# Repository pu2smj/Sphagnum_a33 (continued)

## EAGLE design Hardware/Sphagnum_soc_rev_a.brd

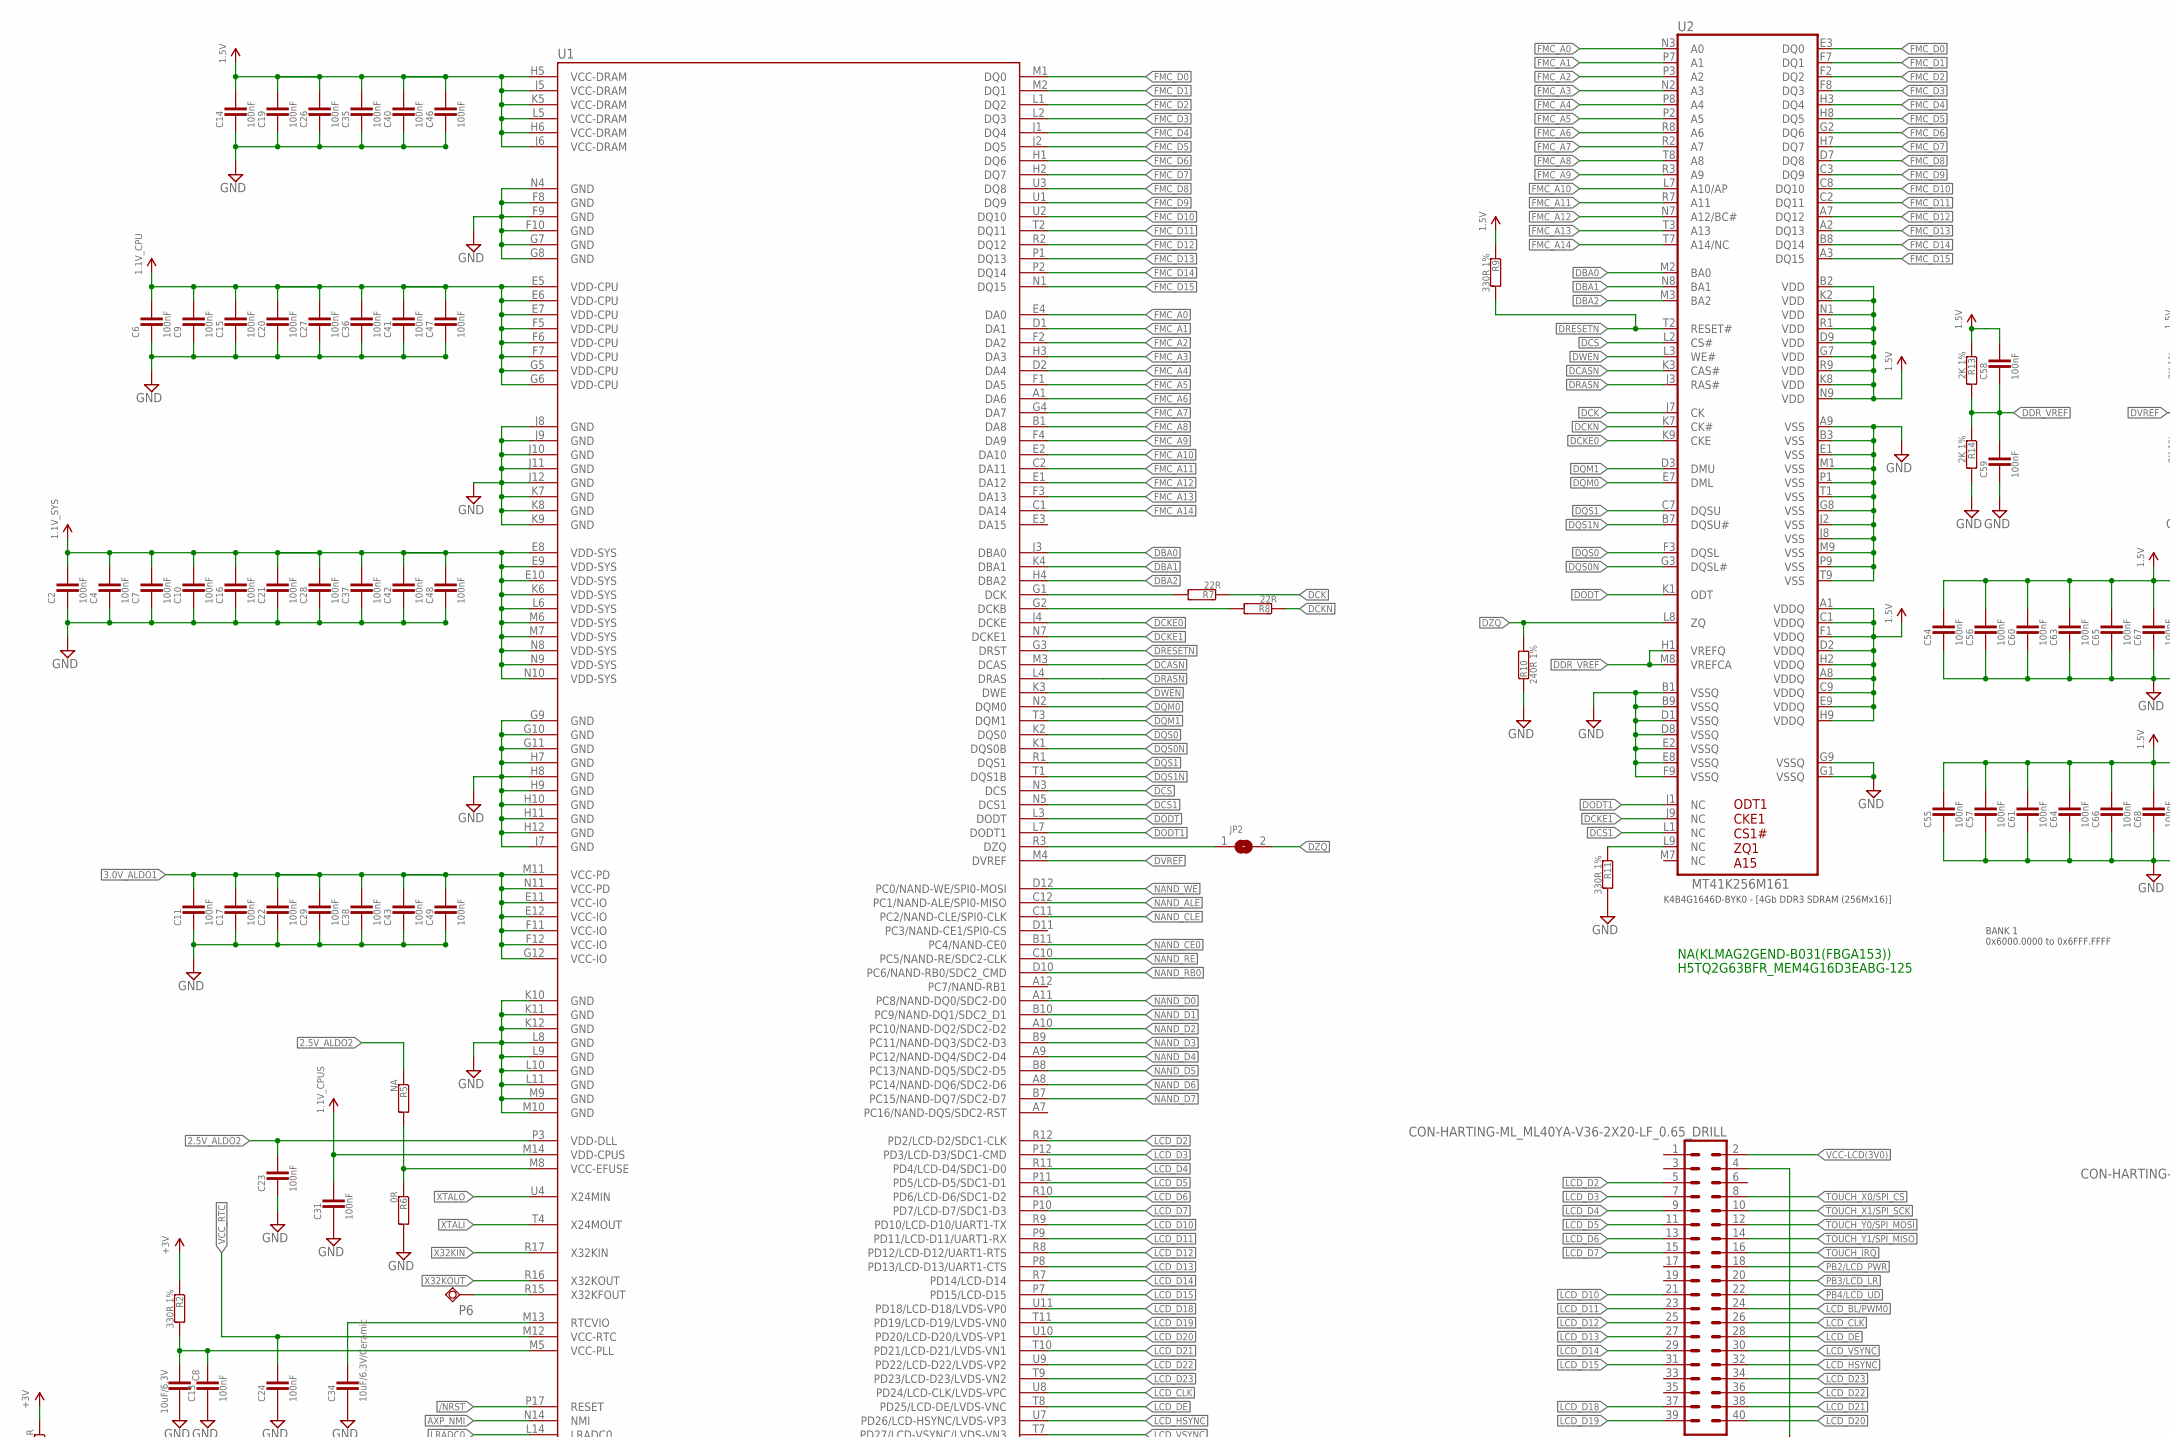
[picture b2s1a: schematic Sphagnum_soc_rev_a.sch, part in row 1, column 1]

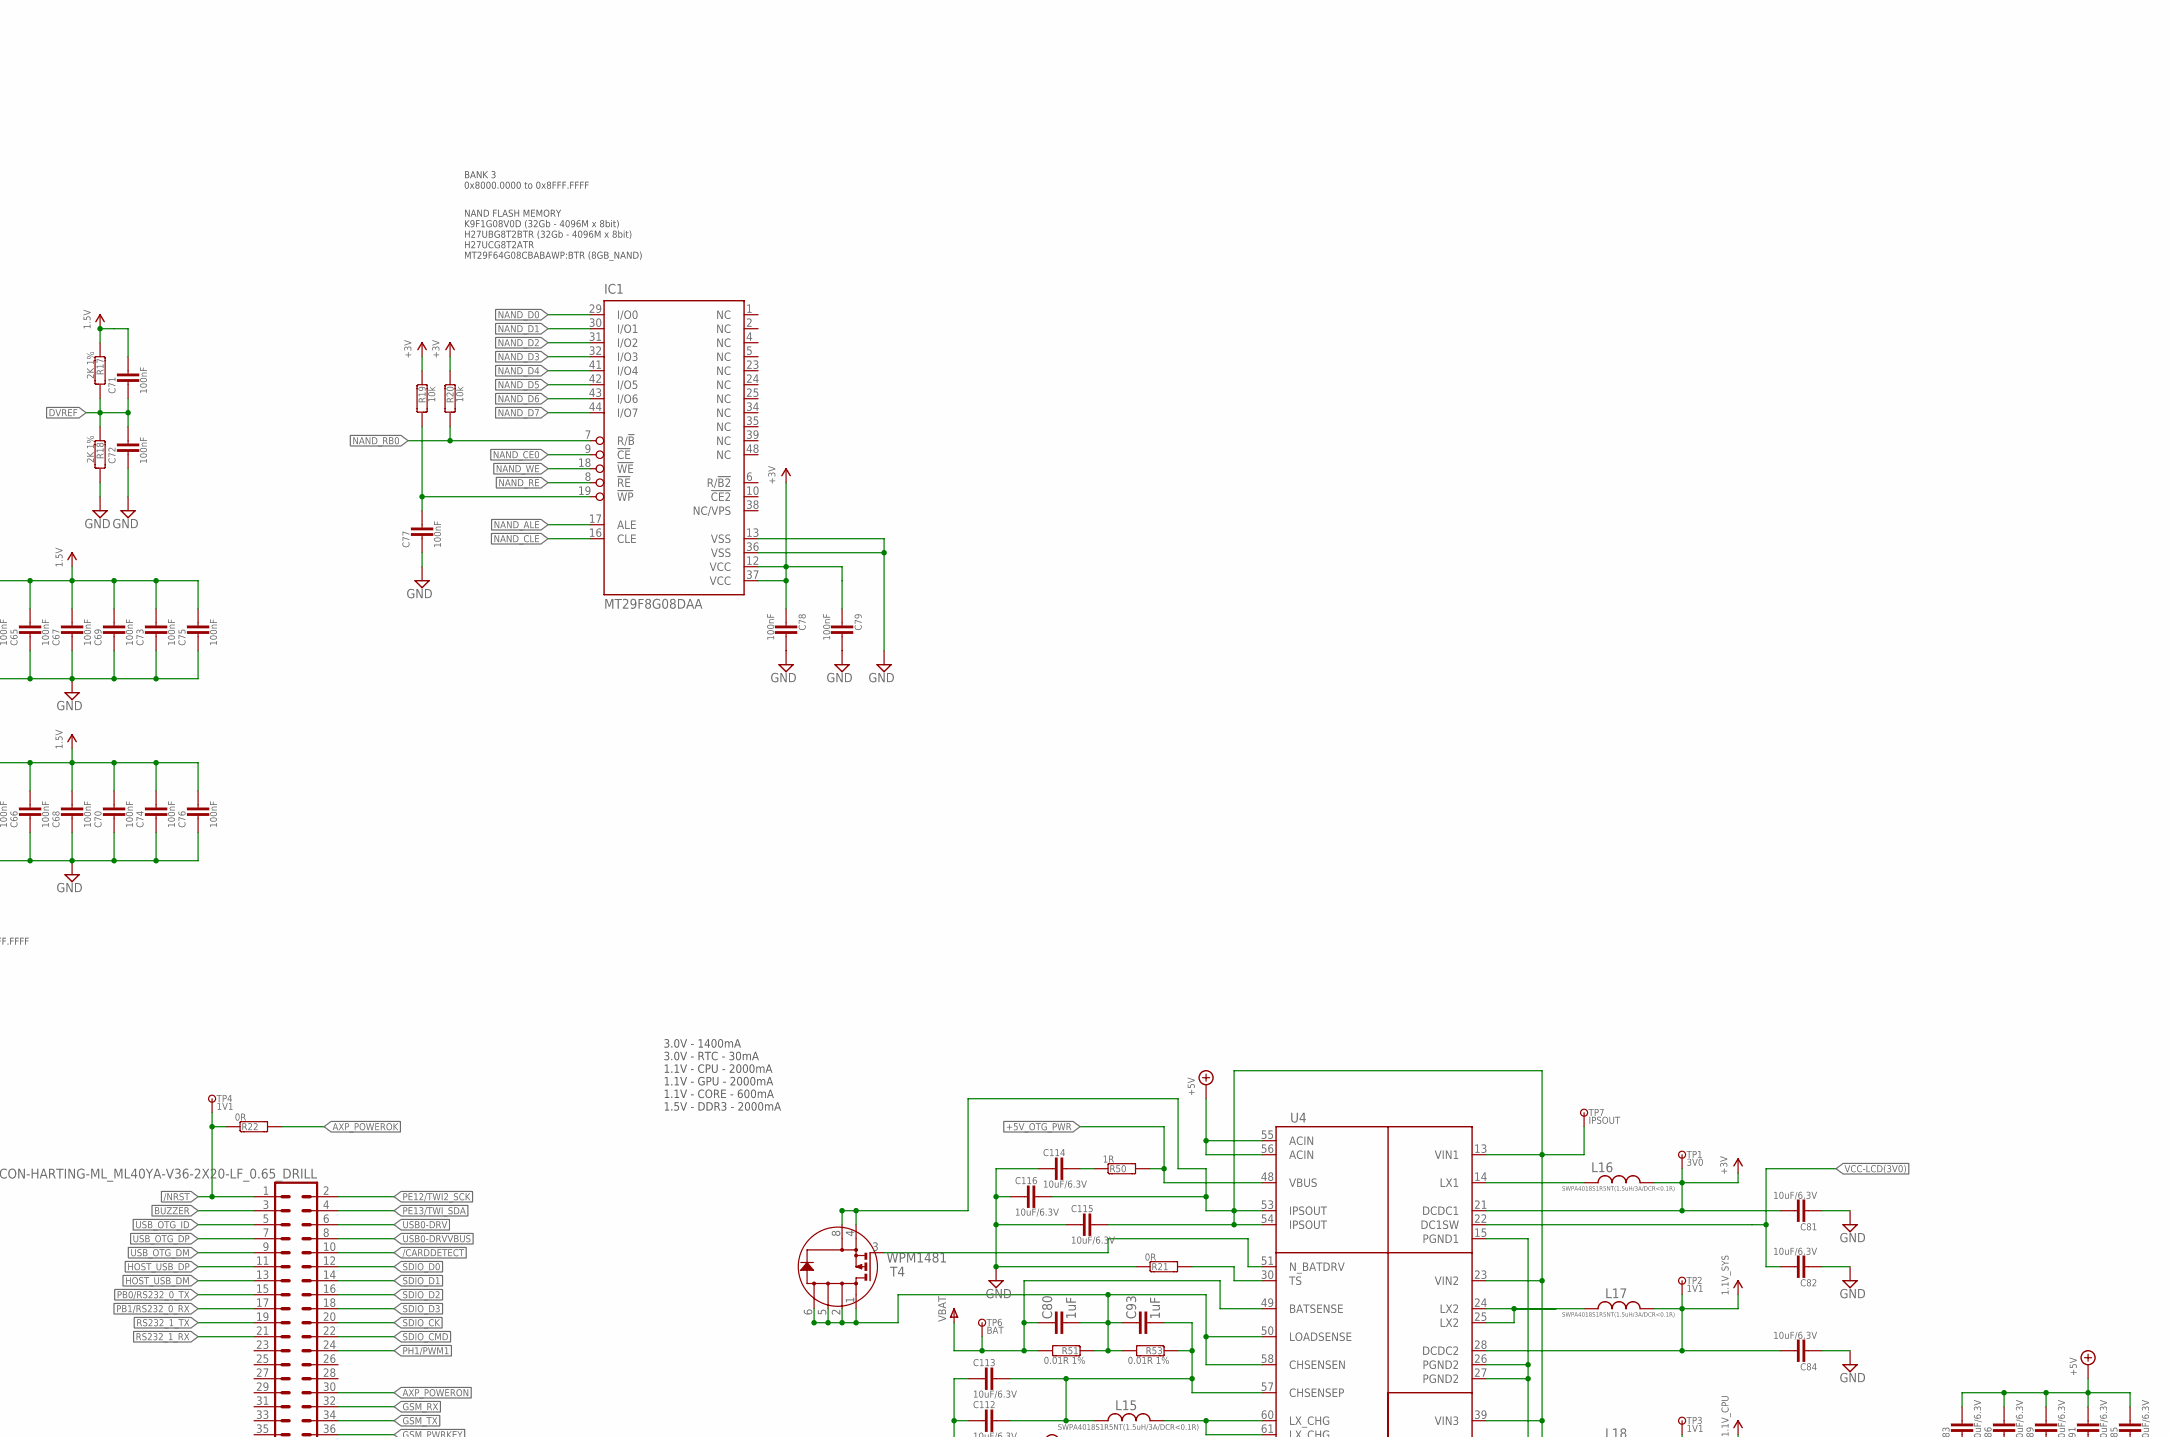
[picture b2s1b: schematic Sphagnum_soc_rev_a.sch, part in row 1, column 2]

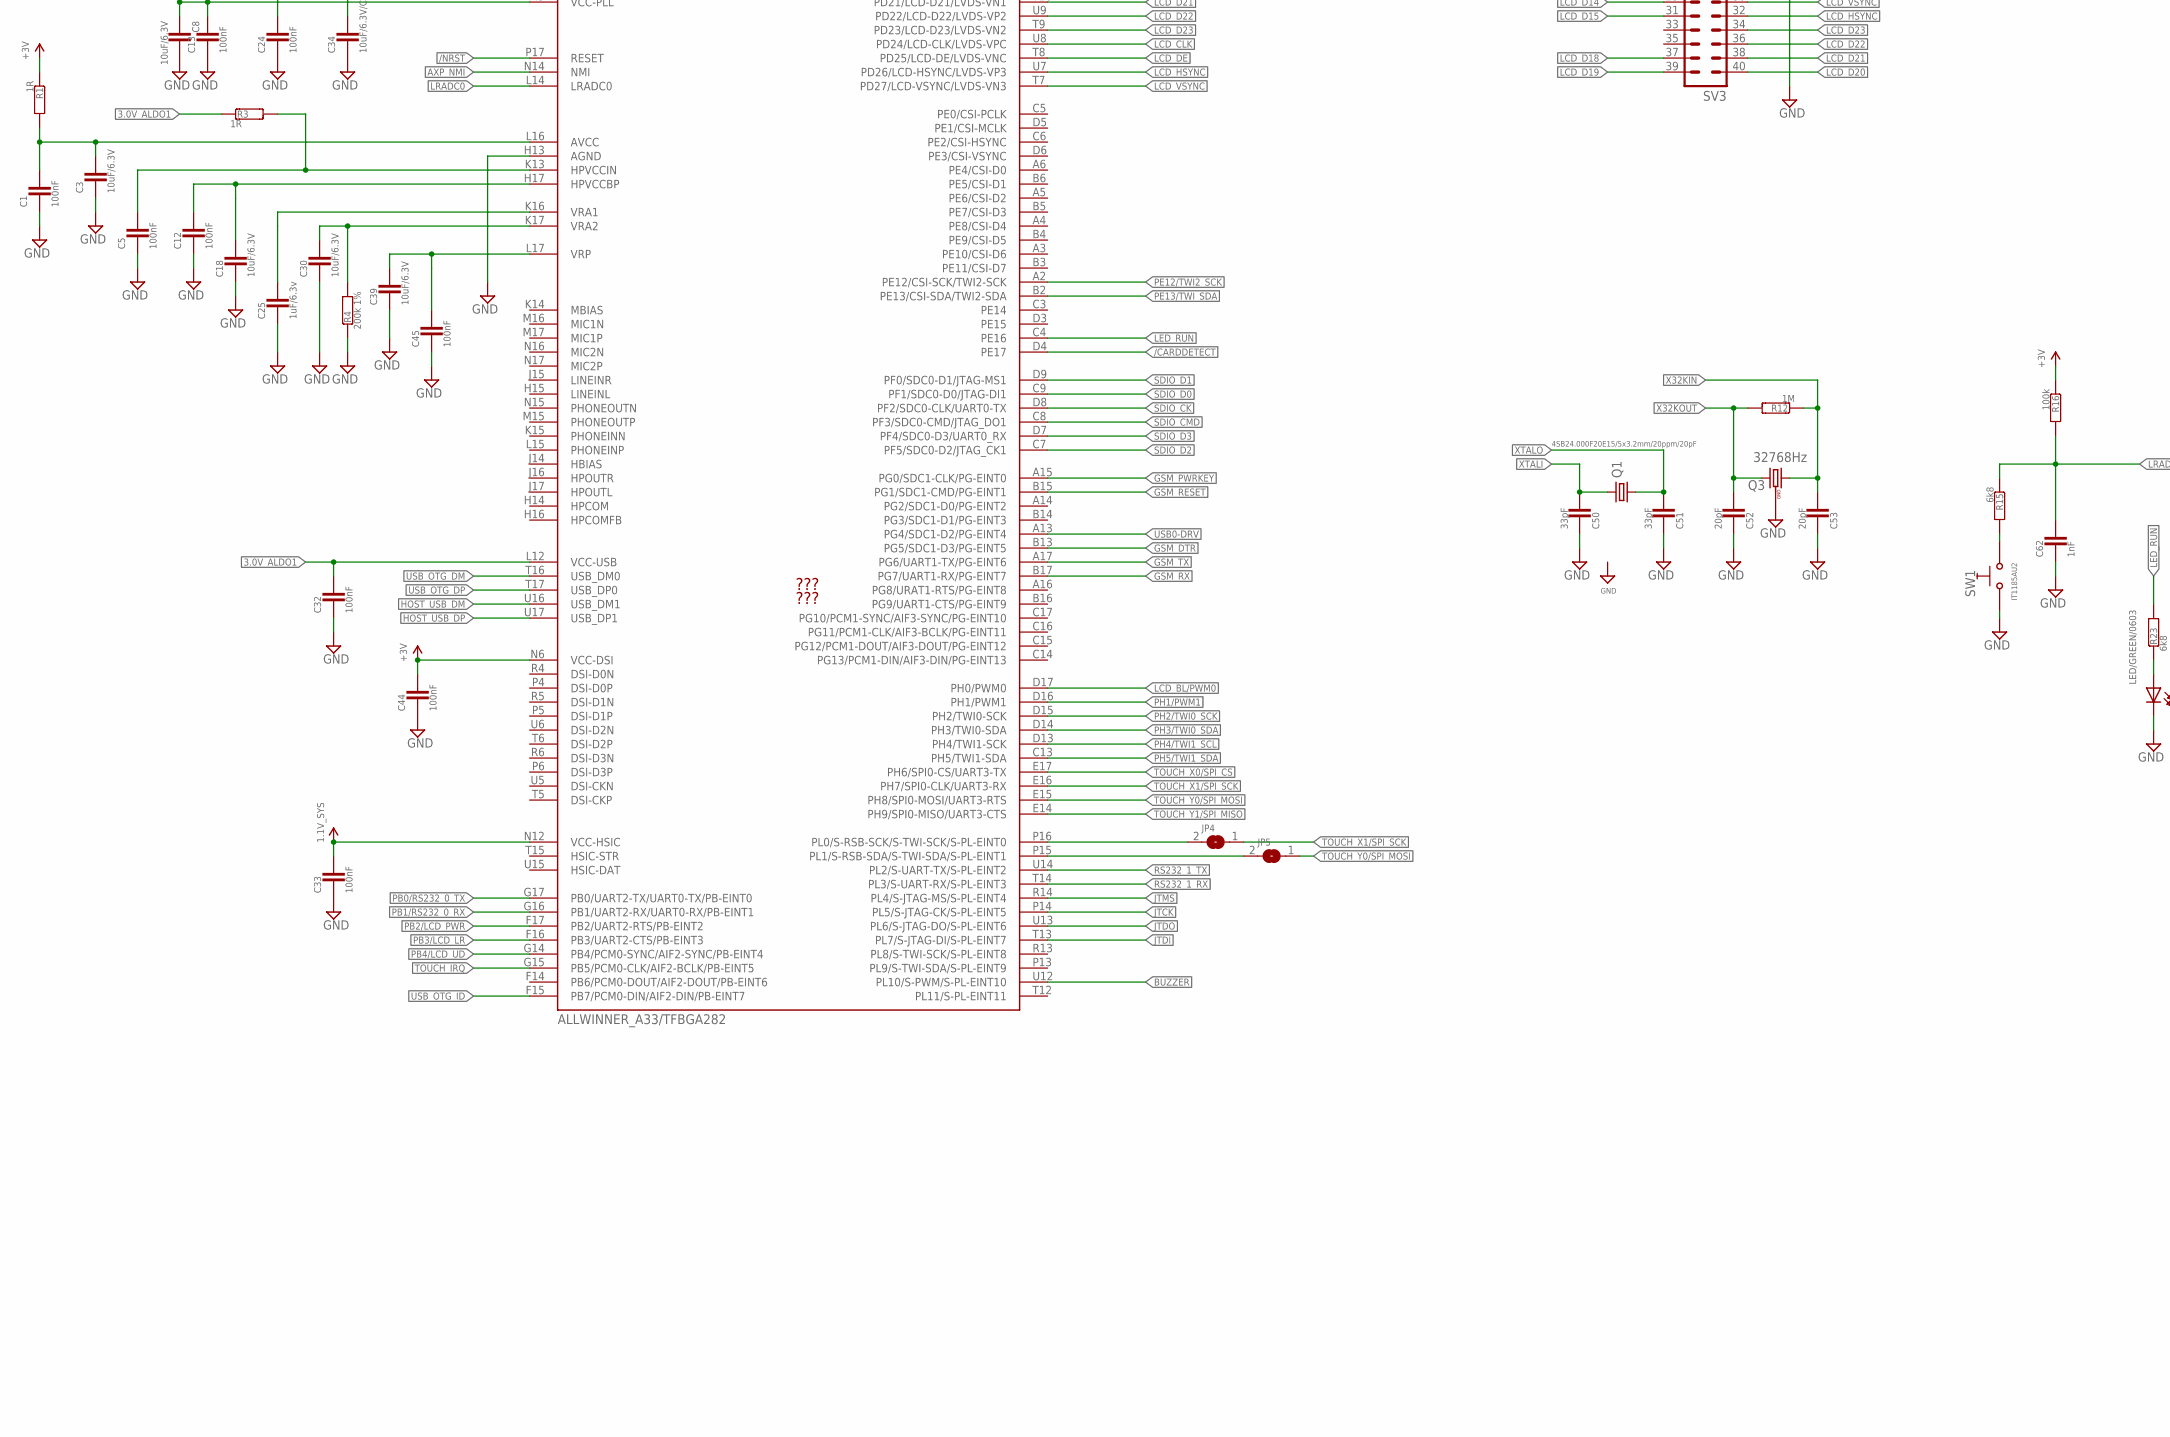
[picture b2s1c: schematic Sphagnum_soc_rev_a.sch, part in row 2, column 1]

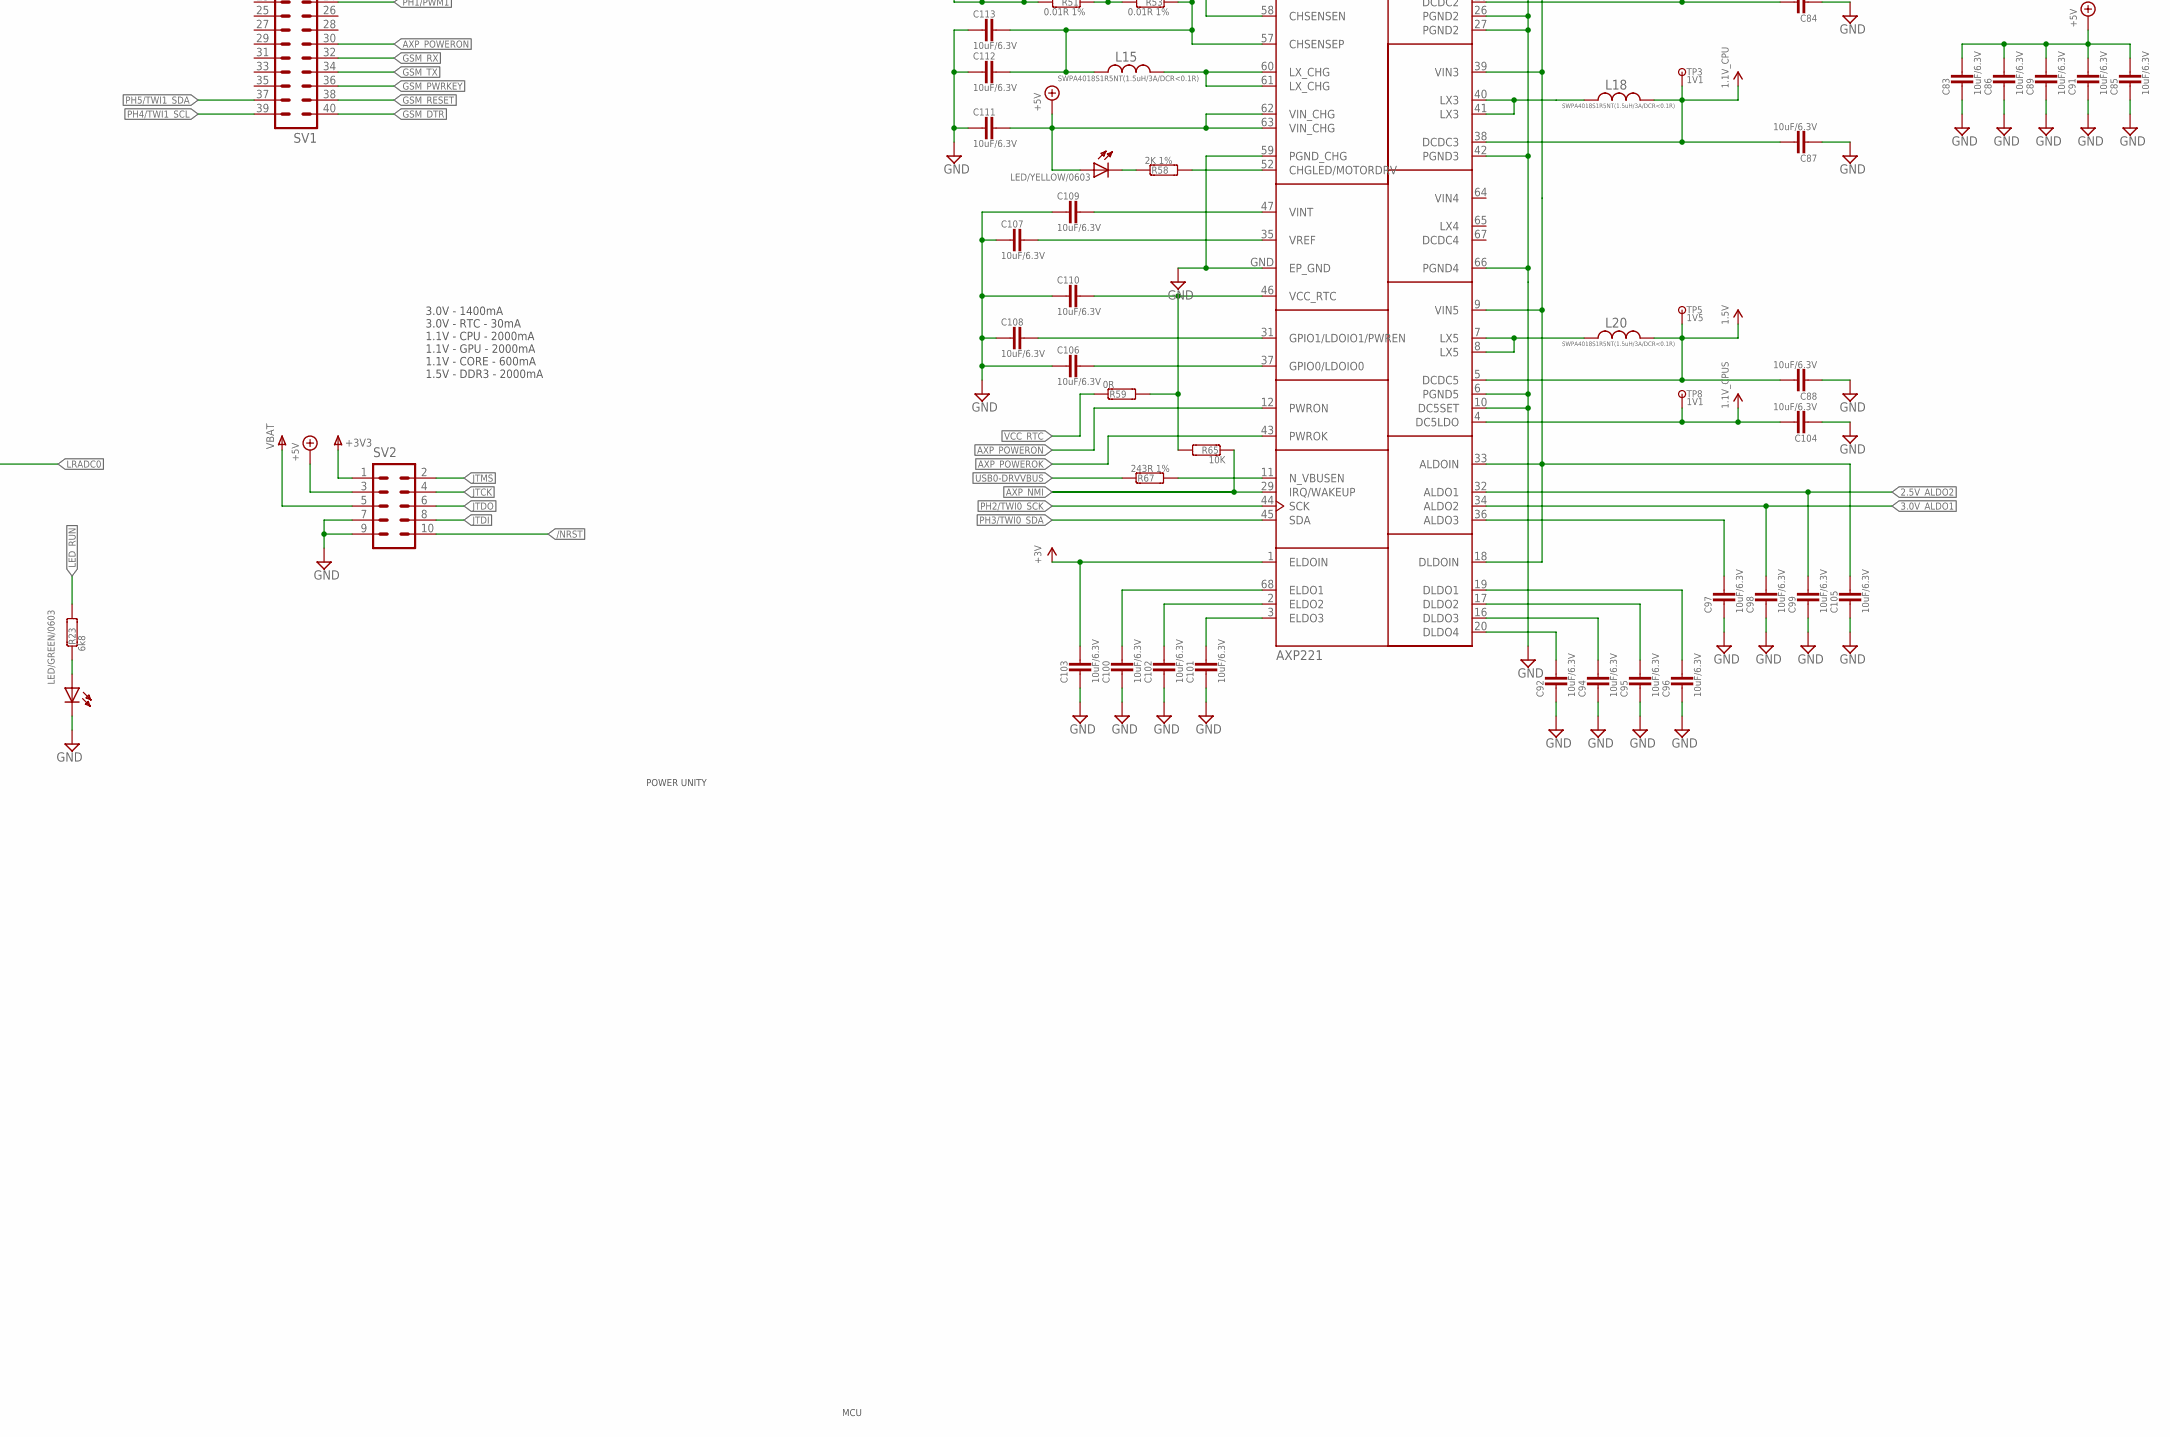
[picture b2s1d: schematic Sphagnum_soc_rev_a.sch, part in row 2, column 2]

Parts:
C1, C2, C4, C5, C6, C7, C9, C10, C11, C12, C13, C14, C15, C16, C17, C19, C20, C21, C22, C23, C24, C26, C27, C28, C29, C31, C32, C33, C35, C36, C37, C38, C40, C41, C42, C43, C44, C45, C46, C47, C48, C49, C54, C55, C56, C57, C58, C59, C60, C61, C63, C64, C65, C66, C67, C68, C69, C70, C71, C72, C73, C74, C75, C76, C77, C78, C79: 100nF; C0603
C3, C8, C18, C30, C39, C81, C82, C83, C84, C85, C86, C87, C88, C89, C91, C92, C94, C95, C96, C97, C98, C99, C100, C101, C102, C103, C104, C105, C106, C107, C108, C109, C110, C111, C112, C113, C114, C115, C116: 10uF/6.3V; C0603
C25: 1uF/6.3v; C0603
C34: 10uF/6.3V/Ceramic; C0603
C50, C51: 33pF; C0603
C52, C53: 20pF; C0603
C62: 1nF; C0603
C80, C93: 1uF; C0603
CHGLED: LED/YELLOW/0603; LED-0603_TEST
IC1: MT29F8G08DAA; TSOP48
JP2: JUMPER-2SMD-NO; SJ_2S-NO
JP4, JP5: JUMPER_2_NO
L15, L16, L17, L18, L20: SWPA4018S1R5NT(1.5uH/3A/DCR<0.1R); SWPA4018S
P6: TESTPADTESTPAD_40-ROUND; TESTPAD_40-ROUND
Q1: 4SB24.000F20E15/5x3.2mm/20ppm/20pF; HCX-4S
Q3: 32768Hz; TC26H_3_REPAIR
R1, R3, R50: 1R; R0603
R2, R9, R11: 330R 1%; R0603
R4: 200k 1%; R0603
R5: NA; R0603
R6, R21, R22, R59: 0R; R0603
R7, R8: 22R; R0603
R10: 240R 1%; R0603
R12: 1M; R0603
R13, R14, R17, R18, R58: 2K 1%; R0603
R15, R23: 6k8; R0603
R16: 100k; R0603
R19, R20: 10k; R0603
R51, R53: 0.01R 1%; R0603
R65: 10K; R0603
R67: 243R 1%; R0603
RUN: LED/GREEN/0603; LED-0603_TEST
SV1, SV3: CON-HARTING-ML_ML40YA-V36-2X20-LF_0.65_DRILL; CON-HARTING-ML_YA-V36P-2X20-LF_0.65_DRILL
SV2: CON-HARTING-ML_ML10YA-V36P-2X5-LF_0.60_DRILL; CON-HARTING-ML_YA-V36P-2X5-LF_0.60_DRILL
SW1: IT1185AU2
T4: WPM1481; DFN2*2-6L
TP1: 3V0; PAD.03X.03
TP2, TP3, TP4, TP8: 1V1; PAD.03X.03
TP5: 1V5; PAD.03X.03
TP6: BAT; PAD.03X.03
TP7: IPSOUT; PAD.03X.03
U1: ALLWINNER_A33/TFBGA282; TFBGA282
U2: MT41K256M161; FBGA_96BALL
U4: AXP221; OLIMEX_IC_QFN68-8X8-04

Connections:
1.1V_CPU: C6.1, C9.1, C15.1, C20.1, C27.1, C36.1, C41.1, C47.1, C87.1, L18.1, TP3.P$1, U1.E5 (VDD-CPU), U1.E6 (VDD-CPU), U1.E7 (VDD-CPU), U1.F5 (VDD-CPU), U1.F6 (VDD-CPU), U1.F7 (VDD-CPU), U1.G5 (VDD-CPU), U1.G6 (VDD-CPU), U4.38 (DCDC3)
1.1V_CPUS: C31.1, C104.1, TP8.P$1, U1.M14 (VDD-CPUS), U4.4 (DC5LDO)
1.1V_SYS: C2.1, C4.1, C7.1, C10.1, C16.1, C21.1, C28.1, C33.1, C37.1, C42.1, C48.1, C84.1, L17.1, TP2.P$1, U1.E8 (VDD-SYS), U1.E9 (VDD-SYS), U1.E10 (VDD-SYS), U1.K6 (VDD-SYS), U1.L6 (VDD-SYS), U1.M6 (VDD-SYS), U1.M7 (VDD-SYS), U1.N8 (VDD-SYS), U1.N9 (VDD-SYS), U1.N10 (VDD-SYS), U1.N12 (VCC-HSIC), U4.28 (DCDC2)
1.5V: C14.1, C19.1, C26.1, C35.1, C40.1, C46.1, C54.1, C55.1, C56.1, C57.1, C58.1, C60.1, C61.1, C63.1, C64.1, C65.1, C66.1, C67.1, C68.1, C69.1, C70.1, C71.1, C73.1, C74.1, C75.1, C76.1, C88.1, L20.1, R9.1, R13.1, R17.1, TP5.P$1, U1.H5 (VCC-DRAM), U1.H6 (VCC-DRAM), U1.J5 (VCC-DRAM), U1.J6 (VCC-DRAM), U1.K5 (VCC-DRAM), U1.L5 (VCC-DRAM), U2.A1 (VDDQ), U2.A8 (VDDQ), U2.B2 (VDD), U2.C1 (VDDQ), U2.C9 (VDDQ), U2.D2 (VDDQ), U2.D9 (VDD), U2.E9 (VDDQ), U2.F1 (VDDQ), U2.G7 (VDD), U2.H2 (VDDQ), U2.H9 (VDDQ), U2.K2 (VDD), U2.K8 (VDD), U2.N1 (VDD), U2.N9 (VDD), U2.R1 (VDD), U2.R9 (VDD), U4.5 (DCDC5)
2.5V_ALDO2: C23.1, C99.1, R5.1, U1.P3 (VDD-DLL), U4.32 (ALDO1)
3.0V_ALDO1: C11.1, C17.1, C22.1, C29.1, C32.1, C38.1, C43.1, C49.1, C98.1, R3.1, U1.E11 (VCC-IO), U1.E12 (VCC-IO), U1.F11 (VCC-IO), U1.F12 (VCC-IO), U1.G12 (VCC-IO), U1.L12 (VCC-USB), U1.M11 (VCC-PD), U1.N11 (VCC-PD), U4.34 (ALDO2)
+3V: C44.1, C78.2, C79.2, C81.1, C103.1, IC1.12 (VCC), IC1.37 (VCC), L16.1, R1.1, R2.1, R16.1, R19.1, R20.1, TP1.P$1, U1.N6 (VCC-DSI), U4.1 (ELDOIN), U4.21 (DCDC1)
+3V3: C80.2, R51.2, SV2.1, SV2.5, TP6.P$1, U4.49 (BATSENSE)
+5V: C83.1, C85.1, C86.1, C89.1, C91.1, C111.1, CHGLED.A, SV2.3, U4.55 (ACIN), U4.56 (ACIN), U4.62 (VIN_CHG), U4.63 (VIN_CHG)
+5V_OTG_PWR: R50.2, U4.48 (VBUS)
/CARDDETECT: SV1.10, U1.D4 (PE17)
/NRST: R22.1, SV1.1, SV2.10, TP4.P$1, U1.P17 (RESET)
AXP_NMI: R65.1, U1.N14 (NMI), U4.29 (IRQ/WAKEUP)
AXP_POWEROK: R22.2, U4.43 (PWROK)
AXP_POWERON: SV1.30, U4.12 (PWRON)
BUZZER: SV1.3, U1.U12 (PL10/S-PWM/S-PL-EINT10)
DBA0: U1.J3 (DBA0), U2.M2 (BA0)
DBA1: U1.K4 (DBA1), U2.N8 (BA1)
DBA2: U1.H4 (DBA2), U2.M3 (BA2)
DCASN: U1.M3 (DCAS), U2.K3 (CAS#)
DCK: R7.1, U2.J7 (CK)
DCKE0: U1.J4 (DCKE), U2.K9 (CKE)
DCKE1: U1.N7 (DCKE1), U2.J9 (NC)
DCKN: R8.1, U2.K7 (CK#)
DCS: U1.N3 (DCS), U2.L2 (CS#)
DCS1: U1.N5 (DCS1), U2.L1 (NC)
DDR_VREF: C58.2, C59.1, R13.2, R14.1, U2.H1 (VREFQ), U2.M8 (VREFCA)
DODT: U1.L3 (DODT), U2.K1 (ODT)
DODT1: U1.L7 (DODT1), U2.J1 (NC)
DQM0: U1.N2 (DQM0), U2.E7 (DML)
DQM1: U1.T3 (DQM1), U2.D3 (DMU)
DQS0: U1.K2 (DQS0), U2.F3 (DQSL)
DQS0N: U1.K1 (DQS0B), U2.G3 (DQSL#)
DQS1: U1.R1 (DQS1), U2.C7 (DQSU)
DQS1N: U1.T1 (DQS1B), U2.B7 (DQSU#)
DRASN: U1.L4 (DRAS), U2.J3 (RAS#)
DRESETN: R9.2, U1.G3 (DRST), U2.T2 (RESET#)
DVREF: C71.2, C72.1, R17.2, R18.1, U1.M4 (DVREF)
DWEN: U1.K3 (DWE), U2.L3 (WE#)
DZQ: JP2.2, R10.2, U2.L8 (ZQ)
FMC_A0: U1.E4 (DA0), U2.N3 (A0)
FMC_A1: U1.D1 (DA1), U2.P7 (A1)
FMC_A2: U1.F2 (DA2), U2.P3 (A2)
FMC_A3: U1.H3 (DA3), U2.N2 (A3)
FMC_A4: U1.D2 (DA4), U2.P8 (A4)
FMC_A5: U1.F1 (DA5), U2.P2 (A5)
FMC_A6: U1.A1 (DA6), U2.R8 (A6)
FMC_A7: U1.G4 (DA7), U2.R2 (A7)
FMC_A8: U1.B1 (DA8), U2.T8 (A8)
FMC_A9: U1.F4 (DA9), U2.R3 (A9)
FMC_A10: U1.E2 (DA10), U2.L7 (A10/AP)
FMC_A11: U1.C2 (DA11), U2.R7 (A11)
FMC_A12: U1.E1 (DA12), U2.N7 (A12/BC#)
FMC_A13: U1.F3 (DA13), U2.T3 (A13)
FMC_A14: U1.C1 (DA14), U2.T7 (A14/NC)
FMC_D0: U1.M1 (DQ0), U2.E3 (DQ0)
FMC_D1: U1.M2 (DQ1), U2.F7 (DQ1)
FMC_D2: U1.L1 (DQ2), U2.F2 (DQ2)
FMC_D3: U1.L2 (DQ3), U2.F8 (DQ3)
FMC_D4: U1.J1 (DQ4), U2.H3 (DQ4)
FMC_D5: U1.J2 (DQ5), U2.H8 (DQ5)
FMC_D6: U1.H1 (DQ6), U2.G2 (DQ6)
FMC_D7: U1.H2 (DQ7), U2.H7 (DQ7)
FMC_D8: U1.U3 (DQ8), U2.D7 (DQ8)
FMC_D9: U1.U1 (DQ9), U2.C3 (DQ9)
FMC_D10: U1.U2 (DQ10), U2.C8 (DQ10)
FMC_D11: U1.T2 (DQ11), U2.C2 (DQ11)
FMC_D12: U1.R2 (DQ12), U2.A7 (DQ12)
FMC_D13: U1.P1 (DQ13), U2.A2 (DQ13)
FMC_D14: U1.P2 (DQ14), U2.B8 (DQ14)
FMC_D15: U1.N1 (DQ15), U2.A3 (DQ15)
GND: C1.2, C2.2, C3.2, C4.2, C5.2, C6.2, C7.2, C8.1, C9.2, C10.2, C11.2, C12.2, C13.2, C14.2, C15.2, C16.2, C17.2, C18.2, C19.2, C20.2, C21.2, C22.2, C23.2, C24.2, C25.2, C26.2, C27.2, C28.2, C29.2, C30.2, C31.2, C32.2, C33.2, C34.2, C35.2, C36.2, C37.2, C38.2, C39.2, C40.2, C41.2, C42.2, C43.2, C44.2, C45.2, C46.2, C47.2, C48.2, C49.2, C50.2, C51.2, C52.2, C53.2, C54.2, C55.2, C56.2, C57.2, C59.2, C60.2, C61.2, C62.2, C63.2, C64.2, C65.2, C66.2, C67.2, C68.2, C69.2, C70.2, C72.2, C73.2, C74.2, C75.2, C76.2, C77.2, C78.1, C79.1, C81.2, C82.2, C83.2, C84.2, C85.2, C86.2, C87.2, C88.2, C89.2, C91.2, C92.2, C94.2, C95.2, C96.2, C97.2, C98.2, C99.2, C100.2, C101.2, C102.2, C103.2, C104.2, C105.2, C106.2, C107.2, C108.2, C109.2, C110.2, C111.2, C112.2, C113.2, C114.2, C115.2, C116.2, IC1.13 (VSS), IC1.36 (VSS), Q3.GND, R4.1, R6.2, R10.1, R11.2, R14.2, R18.2, R21.1, RUN.C, SV2.7, SV2.9, SV3.4, SW1.1 (0), U1.F8 (GND), U1.F9 (GND), U1.F10 (GND), U1.G7 (GND), U1.G8 (GND), U1.G9 (GND), U1.G10 (GND), U1.G11 (GND), U1.H7 (GND), U1.H8 (GND), U1.H9 (GND), U1.H10 (GND), U1.H11 (GND), U1.H12 (GND), U1.H13 (AGND), U1.J7 (GND), U1.J8 (GND), U1.J9 (GND), U1.J10 (GND), U1.J11 (GND), U1.J12 (GND), U1.K7 (GND), U1.K8 (GND), U1.K9 (GND), U1.K10 (GND), U1.K11 (GND), U1.K12 (GND), U1.L8 (GND), U1.L9 (GND), U1.L10 (GND), U1.L11 (GND), U1.M9 (GND), U1.M10 (GND), U1.N4 (GND), U2.A9 (VSS), U2.B1 (VSSQ), U2.B3 (VSS), U2.B9 (VSSQ), U2.D1 (VSSQ), U2.D8 (VSSQ), U2.E1 (VSS), U2.E2 (VSSQ), U2.E8 (VSSQ), U2.F9 (VSSQ), U2.G1 (VSSQ), U2.G8 (VSS), U2.G9 (VSSQ), U2.J2 (VSS), U2.J8 (VSS), U2.M1 (VSS), U2.M9 (VSS), U2.P1 (VSS), U2.P9 (VSS), U2.T1 (VSS), U2.T9 (VSS), U4.6 (PGND5), U4.10 (DC5SET), U4.15 (PGND1), U4.26 (PGND2), U4.27 (PGND2), U4.42 (PGND3), U4.59 (PGND_CHG), U4.66 (PGND4), U4.GND (EP_GND)
GSM_DTR: SV1.40, U1.B13 (PG5/SDC1-D3/PG-EINT5)
GSM_PWRKEY: SV1.36, U1.A15 (PG0/SDC1-CLK/PG-EINT0)
GSM_RESET: SV1.38, U1.B15 (PG1/SDC1-CMD/PG-EINT1)
GSM_RX: SV1.32, U1.B17 (PG7/UART1-RX/PG-EINT7)
GSM_TX: SV1.34, U1.A17 (PG6/UART1-TX/PG-EINT6)
HOST_USB_DM: SV1.13, U1.U16 (USB_DM1)
HOST_USB_DP: SV1.11, U1.U17 (USB_DP1)
HPVCCIN: C5.1, R3.2, U1.K13 (HPVCCIN)
JTCK: SV2.4, U1.P14 (PL5/S-JTAG-CK/S-PL-EINT5)
JTDI: SV2.8, U1.T13 (PL7/S-JTAG-DI/S-PL-EINT7)
JTDO: SV2.6, U1.U13 (PL6/S-JTAG-DO/S-PL-EINT6)
JTMS: SV2.2, U1.R14 (PL4/S-JTAG-MS/S-PL-EINT4)
LCD_BL/PWM0: SV3.24, U1.D17 (PH0/PWM0)
LCD_CLK: SV3.26, U1.U8 (PD24/LCD-CLK/LVDS-VPC)
LCD_D2: SV3.5, U1.R12 (PD2/LCD-D2/SDC1-CLK)
LCD_D3: SV3.7, U1.P12 (PD3/LCD-D3/SDC1-CMD)
LCD_D4: SV3.9, U1.R11 (PD4/LCD-D4/SDC1-D0)
LCD_D5: SV3.11, U1.P11 (PD5/LCD-D5/SDC1-D1)
LCD_D6: SV3.13, U1.R10 (PD6/LCD-D6/SDC1-D2)
LCD_D7: SV3.15, U1.P10 (PD7/LCD-D7/SDC1-D3)
LCD_D10: SV3.21, U1.R9 (PD10/LCD-D10/UART1-TX)
LCD_D11: SV3.23, U1.P9 (PD11/LCD-D11/UART1-RX)
LCD_D12: SV3.25, U1.R8 (PD12/LCD-D12/UART1-RTS)
LCD_D13: SV3.27, U1.P8 (PD13/LCD-D13/UART1-CTS)
LCD_D14: SV3.29, U1.R7 (PD14/LCD-D14)
LCD_D15: SV3.31, U1.P7 (PD15/LCD-D15)
LCD_D18: SV3.37, U1.U11 (PD18/LCD-D18/LVDS-VP0)
LCD_D19: SV3.39, U1.T11 (PD19/LCD-D19/LVDS-VN0)
LCD_D20: SV3.40, U1.U10 (PD20/LCD-D20/LVDS-VP1)
LCD_D21: SV3.38, U1.T10 (PD21/LCD-D21/LVDS-VN1)
LCD_D22: SV3.36, U1.U9 (PD22/LCD-D22/LVDS-VP2)
LCD_D23: SV3.34, U1.T9 (PD23/LCD-D23/LVDS-VN2)
LCD_DE: SV3.28, U1.T8 (PD25/LCD-DE/LVDS-VNC)
LCD_HSYNC: SV3.32, U1.U7 (PD26/LCD-HSYNC/LVDS-VP3)
LCD_VSYNC: SV3.30, U1.T7 (PD27/LCD-VSYNC/LVDS-VN3)
LED_RUN: R23.2, U1.C4 (PE16)
LRADC0: C62.1, R15.1, R16.2, U1.L14 (LRADC0)
unnamed: JP2.1, U1.R3 (DZQ)
unnamed: R5.2, R6.1, U1.M8 (VCC-EFUSE)
unnamed: JP5.2 (5), U1.P15 (PL1/S-RSB-SDA/S-TWI-SDA/S-PL-EINT1)
unnamed: R11.1, U2.L9 (NC)
unnamed: C77.1, IC1.19 (!WP), R19.2
unnamed: C34.1, U1.M13 (RTCVIO)
unnamed: JP4.2 (5), U1.P16 (PL0/S-RSB-SCK/S-TWI-SCK/S-PL-EINT0)
unnamed: C8.2, C13.1, R2.2, U1.M5 (VCC-PLL)
unnamed: T4.3 (G), U4.51 (N_BATDRV)
unnamed: C80.1, C93.2, R51.1, R53.2, T4.1 (D), T4.2 (D1), T4.5 (D2), T4.6 (D3), T4.7 (D4), U4.50 (LOADSENSE), U4.58 (CHSENSEN)
unnamed: R7.2, U1.G1 (DCK)
unnamed: R8.2, U1.G2 (DCKB)
unnamed: R23.1, RUN.A
unnamed: C105.1, C115.1, C116.1, T4.4 (S), T4.8 (S1), TP7.P$1, U4.9 (VIN5), U4.13 (VIN1), U4.18 (DLDOIN), U4.23 (VIN2), U4.33 (ALDOIN), U4.39 (VIN3), U4.53 (IPSOUT), U4.54 (IPSOUT)
unnamed: C12.1, C18.1, U1.H17 (HPVCCBP)
unnamed: C25.1, U1.K16 (VRA1)
unnamed: C1.1, C3.1, R1.2, U1.L16 (AVCC)
unnamed: R15.2, SW1.2 (1)
unnamed: P6.1, U1.R15 (X32KFOUT)
unnamed: L15.1, U4.60 (LX_CHG), U4.61 (LX_CHG)
unnamed: CHGLED.C, R58.1
unnamed: C93.1, C112.1, C113.1, L15.2, R53.1, U4.57 (CHSENSEP)
unnamed: C106.1, U4.37 (GPIO0/LDOIO0)
unnamed: C108.1, U4.31 (GPIO1/LDOIO1/PWREN)
unnamed: C92.1, U4.20 (DLDO4)
unnamed: C94.1, U4.16 (DLDO3)
unnamed: L16.2, U4.14 (LX1)
unnamed: L17.2, U4.24 (LX2), U4.25 (LX2)
unnamed: L18.2, U4.40 (LX3), U4.41 (LX3)
unnamed: L20.2, U4.7 (LX5), U4.8 (LX5)
unnamed: R67.2, U4.11 (N_VBUSEN)
unnamed: R21.2, U4.30 (TS)
unnamed: C95.1, U4.17 (DLDO2)
unnamed: C96.1, U4.19 (DLDO1)
unnamed: C97.1, U4.36 (ALDO3)
unnamed: C101.1, U4.3 (ELDO3)
unnamed: C102.1, U4.2 (ELDO2)
unnamed: C100.1, U4.68 (ELDO1)
unnamed: C110.1, R59.2, R65.2, U4.46 (VCC_RTC)
unnamed: C107.1, U4.35 (VREF)
unnamed: C109.1, U4.47 (VINT)
unnamed: R58.2, U4.52 (CHGLED/MOTORDRV)
unnamed: C39.1, C45.1, U1.L17 (VRP)
unnamed: C114.1, R50.1
unnamed: C30.1, R4.2, U1.K17 (VRA2)
NAND_ALE: IC1.17 (ALE), U1.C12 (PC1/NAND-ALE/SPI0-MISO)
NAND_CE0: IC1.9 (!CE), U1.B11 (PC4/NAND-CE0)
NAND_CLE: IC1.16 (CLE), U1.C11 (PC2/NAND-CLE/SPI0-CLK)
NAND_D0: IC1.29 (I/O0), U1.A11 (PC8/NAND-DQ0/SDC2-D0)
NAND_D1: IC1.30 (I/O1), U1.B10 (PC9/NAND-DQ1/SDC2_D1)
NAND_D2: IC1.31 (I/O2), U1.A10 (PC10/NAND-DQ2/SDC2-D2)
NAND_D3: IC1.32 (I/O3), U1.B9 (PC11/NAND-DQ3/SDC2-D3)
NAND_D4: IC1.41 (I/O4), U1.A9 (PC12/NAND-DQ4/SDC2-D4)
NAND_D5: IC1.42 (I/O5), U1.B8 (PC13/NAND-DQ5/SDC2-D5)
NAND_D6: IC1.43 (I/O6), U1.A8 (PC14/NAND-DQ6/SDC2-D6)
NAND_D7: IC1.44 (I/O7), U1.B7 (PC15/NAND-DQ7/SDC2-D7)
NAND_RB0: IC1.7 (R/!B), R20.2, U1.D10 (PC6/NAND-RB0/SDC2_CMD)
NAND_RE: IC1.8 (!RE), U1.C10 (PC5/NAND-RE/SDC2-CLK)
NAND_WE: IC1.18 (!WE), U1.D12 (PC0/NAND-WE/SPI0-MOSI)
PB0/RS232_0_TX: SV1.15, U1.G17 (PB0/UART2-TX/UART0-TX/PB-EINT0)
PB1/RS232_0_RX: SV1.17, U1.G16 (PB1/UART2-RX/UART0-RX/PB-EINT1)
PB2/LCD_PWR: SV3.18, U1.F17 (PB2/UART2-RTS/PB-EINT2)
PB3/LCD_LR: SV3.20, U1.F16 (PB3/UART2-CTS/PB-EINT3)
PB4/LCD_UD: SV3.22, U1.G14 (PB4/PCM0-SYNC/AIF2-SYNC/PB-EINT4)
PE12/TWI2_SCK: SV1.2, U1.A2 (PE12/CSI-SCK/TWI2-SCK)
PE13/TWI_SDA: SV1.4, U1.B2 (PE13/CSI-SDA/TWI2-SDA)
PH1/PWM1: SV1.24, U1.D16 (PH1/PWM1)
PH2/TWI0_SCK: U1.D15 (PH2/TWI0-SCK), U4.44 (SCK)
PH3/TWI0_SDA: U1.D14 (PH3/TWI0-SDA), U4.45 (SDA)
PH4/TWI1_SCL: SV1.39, U1.D13 (PH4/TWI1-SCK)
PH5/TWI1_SDA: SV1.37, U1.C13 (PH5/TWI1-SDA)
RS232_1_RX: SV1.21, U1.T14 (PL3/S-UART-RX/S-PL-EINT3)
RS232_1_TX: SV1.19, U1.U14 (PL2/S-UART-TX/S-PL-EINT2)
SDIO_CK: SV1.20, U1.D8 (PF2/SDC0-CLK/UART0-TX)
SDIO_CMD: SV1.22, U1.C8 (PF3/SDC0-CMD/JTAG_DO1)
SDIO_D0: SV1.12, U1.C9 (PF1/SDC0-D0/JTAG-DI1)
SDIO_D1: SV1.14, U1.D9 (PF0/SDC0-D1/JTAG-MS1)
SDIO_D2: SV1.16, U1.C7 (PF5/SDC0-D2/JTAG_CK1)
SDIO_D3: SV1.18, U1.D7 (PF4/SDC0-D3/UART0_RX)
TOUCH_IRQ: SV3.16, U1.G15 (PB5/PCM0-CLK/AIF2-BCLK/PB-EINT5)
TOUCH_X0/SPI_CS: SV3.8, U1.E17 (PH6/SPI0-CS/UART3-TX)
TOUCH_X1/SPI_SCK: JP4.1 (4), SV3.10, U1.E16 (PH7/SPI0-CLK/UART3-RX)
TOUCH_Y0/SPI_MOSI: JP5.1 (4), SV3.12, U1.E15 (PH8/SPI0-MOSI/UART3-RTS)
TOUCH_Y1/SPI_MISO: SV3.14, U1.E14 (PH9/SPI0-MISO/UART3-CTS)
USB0-DRV: SV1.6, U1.A13 (PG4/SDC1-D2/PG-EINT4)
USB0-DRVVBUS: R67.1, SV1.8
USB_OTG_DM: SV1.9, U1.T16 (USB_DM0)
USB_OTG_DP: SV1.7, U1.T17 (USB_DP0)
USB_OTG_ID: SV1.5, U1.F15 (PB7/PCM0-DIN/AIF2-DIN/PB-EINT7)
VCC-LCD(3V0): C82.1, SV3.2, U4.22 (DC1SW)
VCC_RTC: C24.1, R59.1, U1.M12 (VCC-RTC)
X32KIN: C53.1, Q3.1, R12.1, U1.R17 (X32KIN)
X32KOUT: C52.1, Q3.2, R12.2, U1.R16 (X32KOUT)
XTALI: C50.1, Q1.2, U1.T4 (X24MOUT)
XTALO: C51.1, Q1.1, U1.U4 (X24MIN)

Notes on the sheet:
MCU
NAND FLASH MEMORY K9F1G08V0D (32Gb - 4096M x 8bit) H27UBG8T2BTR (32Gb - 4096M x 8bit) H27UCG8T2ATR MT29F64G08CBABAWP:BTR (8GB_NAND)
BANK 3 0x8000.0000 to 0x8FFF.FFFF
BANK 1 0x6000.0000 to 0x6FFF.FFFF
NA(KLMAG2GEND-B031(FBGA153))
H5TQ2G63BFR_MEM4G16D3EABG-125
K4B4G1646D-BYK0 - [4Gb DDR3 SDRAM (256Mx16)]
3.0V - 1400mA 3.0V - RTC - 30mA 1.1V - CPU - 2000mA 1.1V - GPU - 2000mA 1.1V - CORE - 600mA 1.5V - DDR3 - 2000mA
POWER UNITY

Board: 4 copper layers, 175 parts (84 on the bottom side), 204 nets, no tracks yet.

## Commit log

2023-02-06 initial version
    initial vesion revision a
